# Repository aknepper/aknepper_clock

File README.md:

# aknepper_clock
 Google HPS Clock

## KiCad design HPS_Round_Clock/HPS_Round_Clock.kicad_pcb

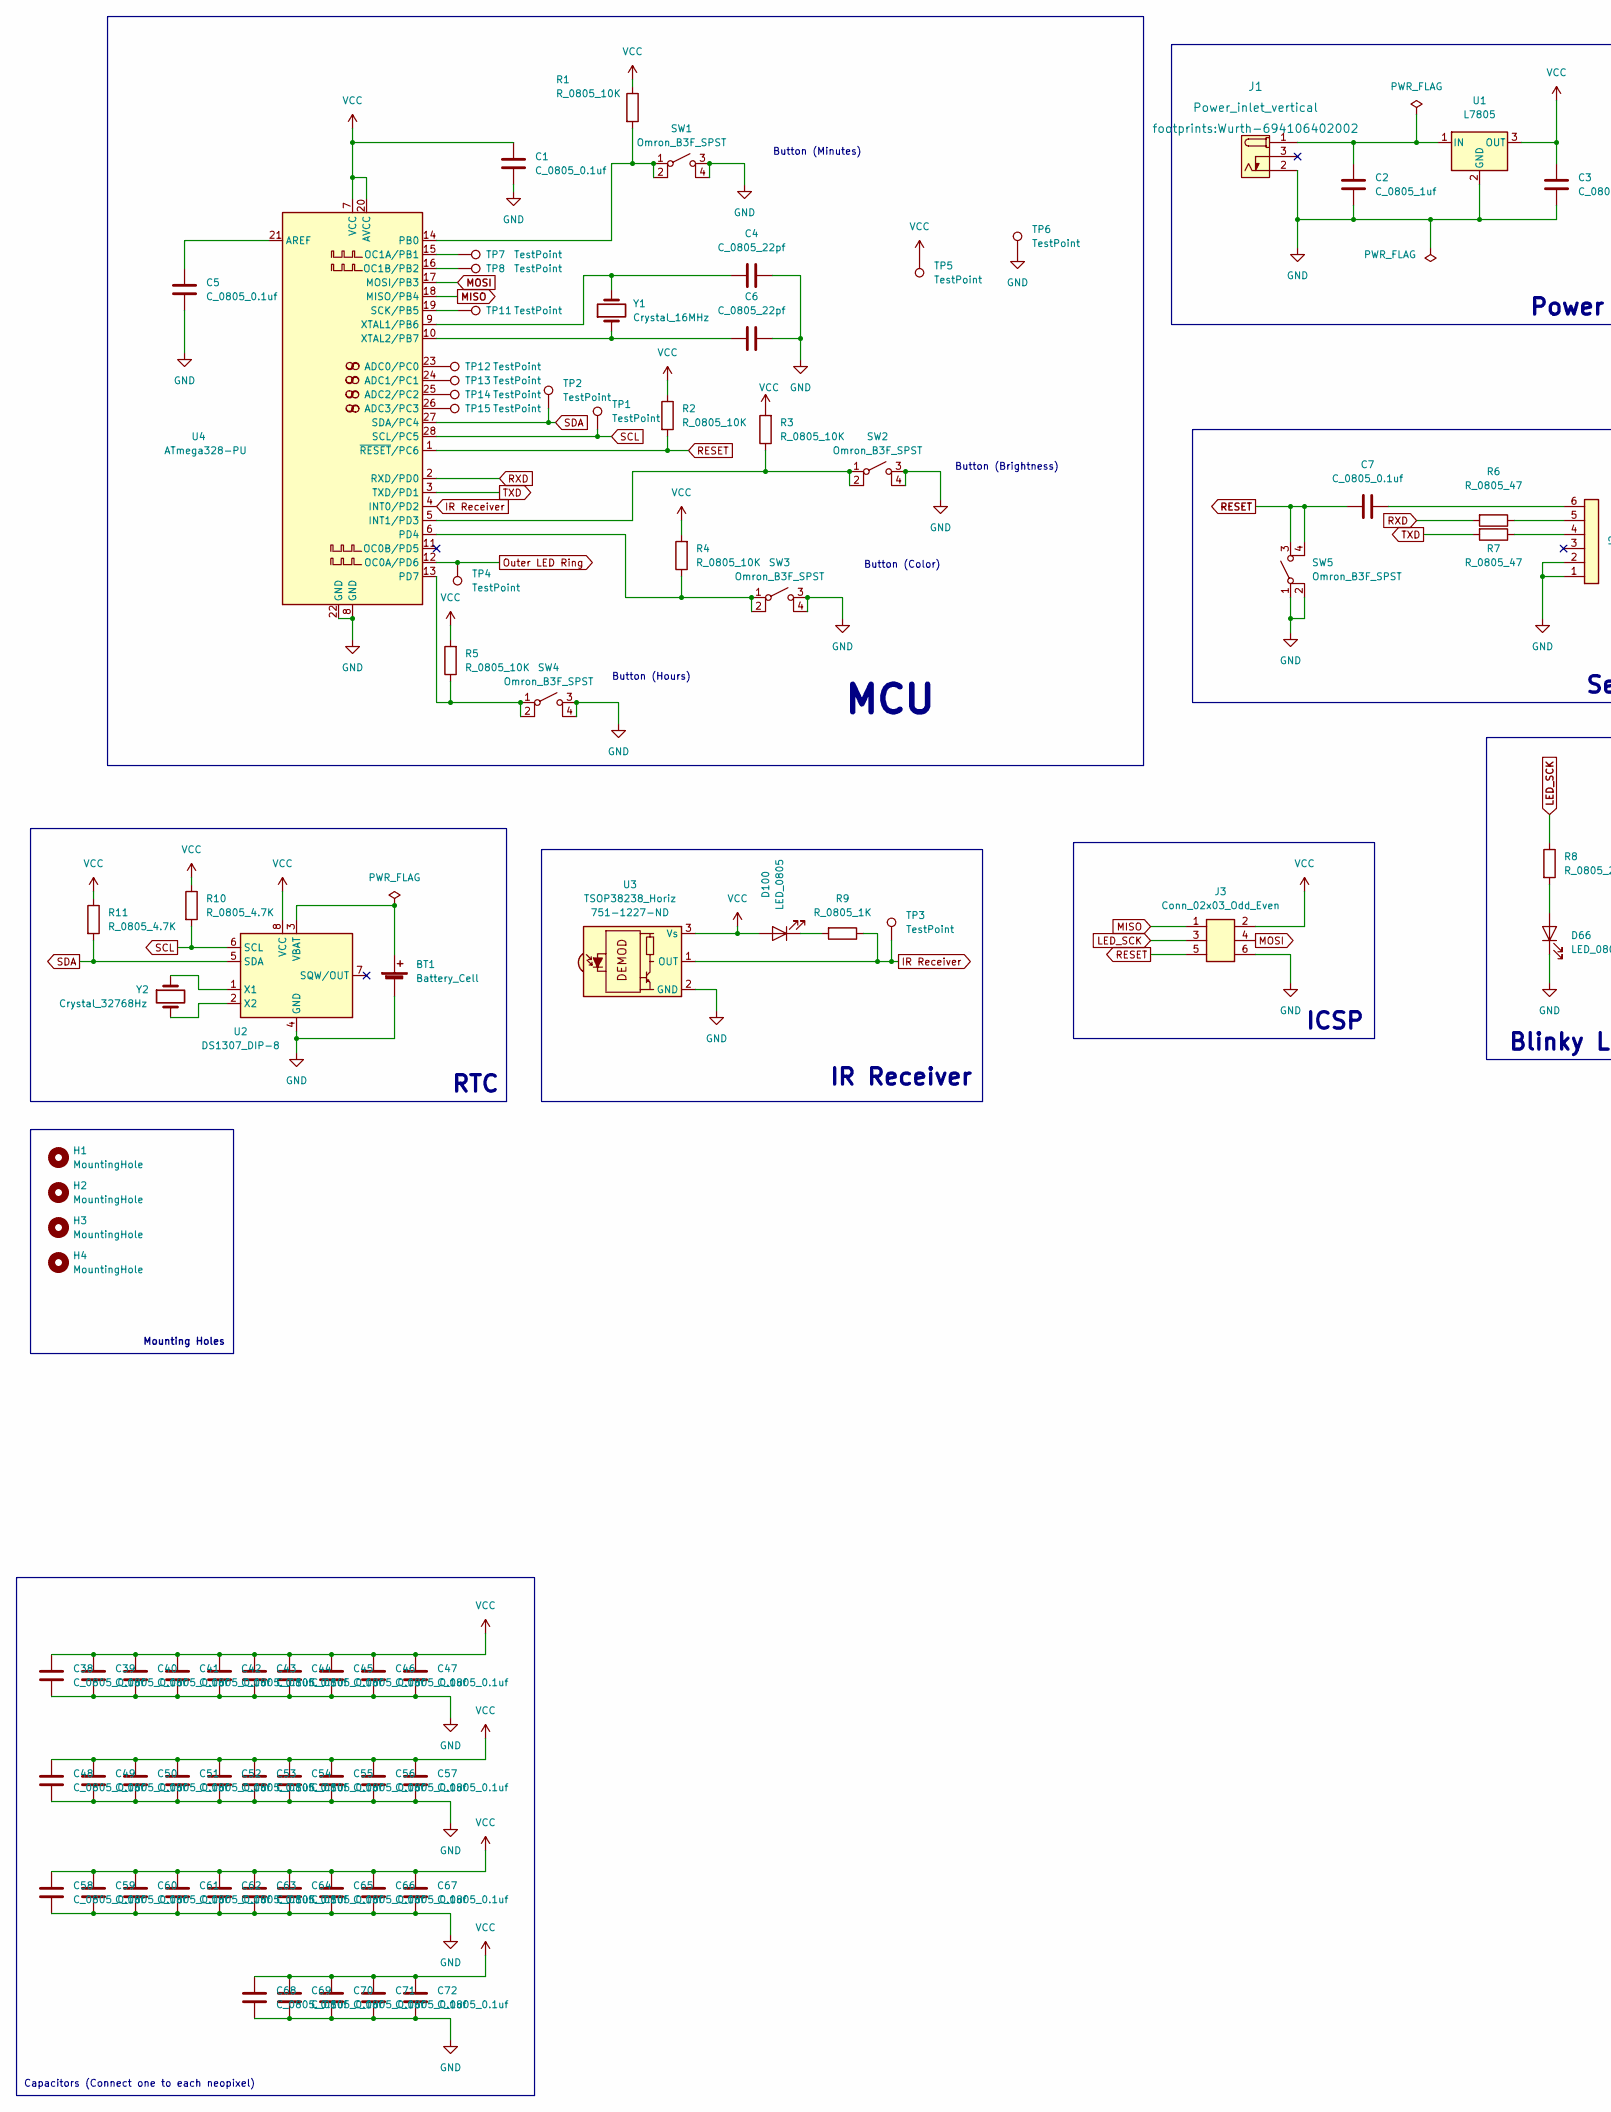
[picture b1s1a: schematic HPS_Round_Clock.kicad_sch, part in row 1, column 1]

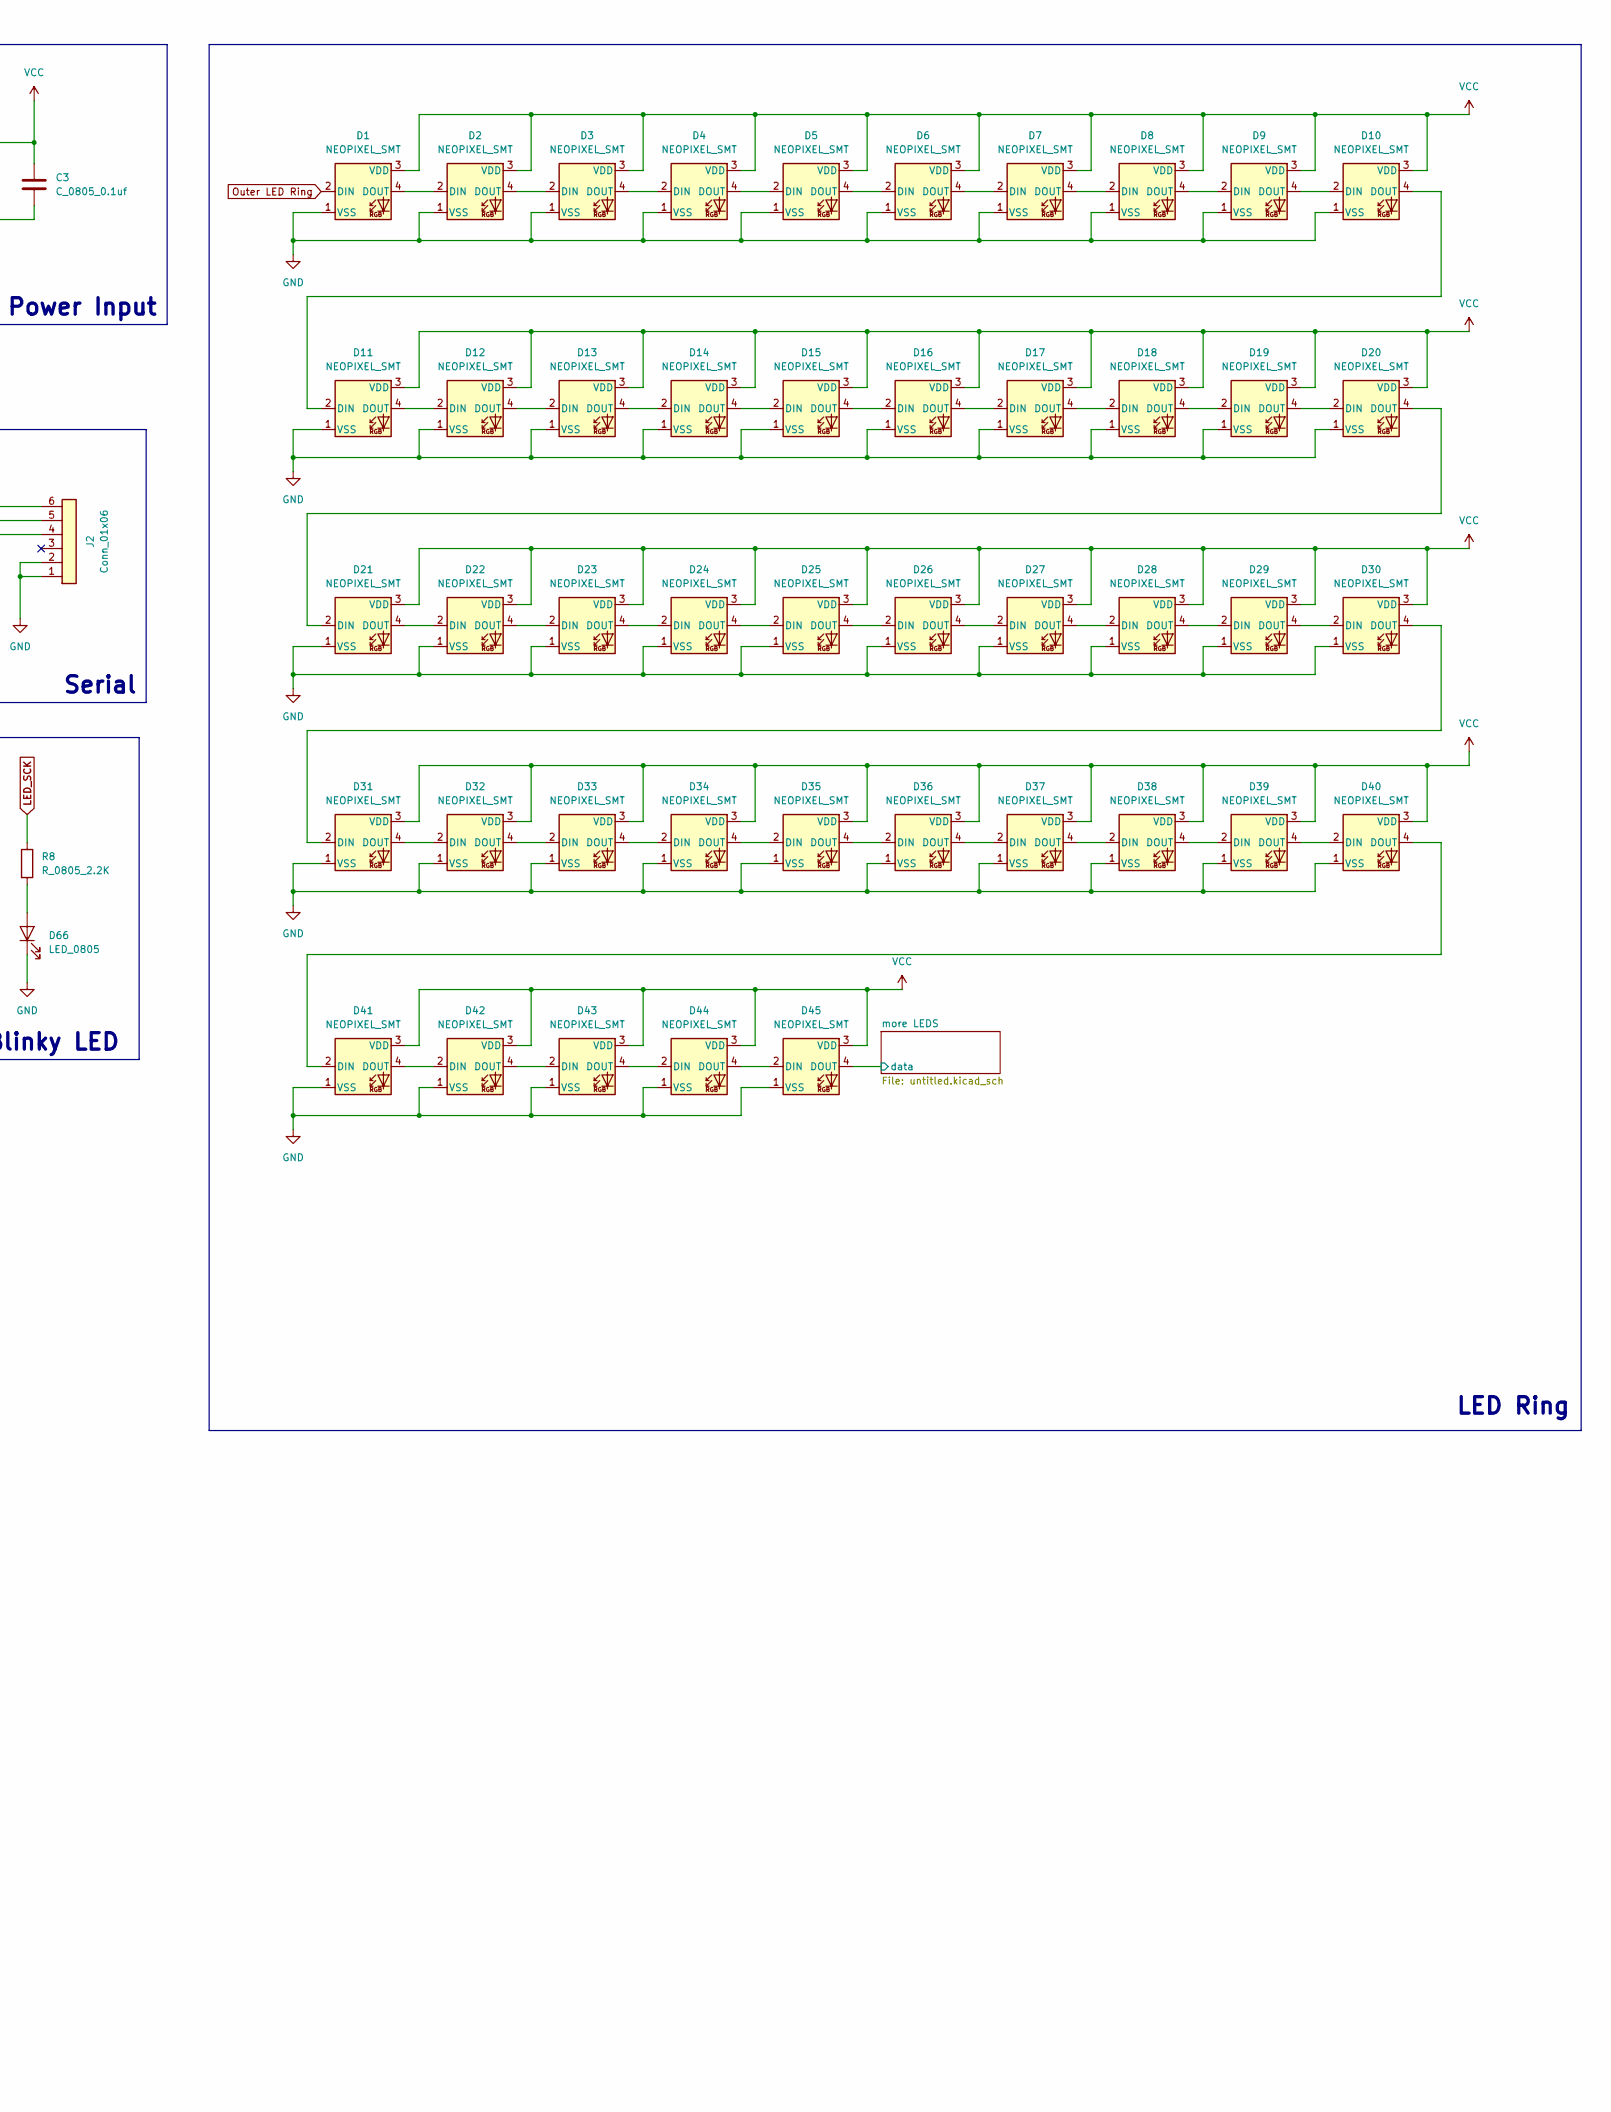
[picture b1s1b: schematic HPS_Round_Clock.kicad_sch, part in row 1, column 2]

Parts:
BT1: Battery_Cell; BatteryHolder_Keystone_106_1x20mm; MPN BS-7; Digikey PN BS-7-ND
C1, C3, C5, C7, C38, C39, C40, C41, C42, C43, C44, C45, C46, C47, C48, C49, C50, C51, C52, C53, C54, C55, C56, C57, C58, C59, C60, C61, C62, C63, C64, C65, C66, C67, C68, C69, C70, C71, C72: C_0805_0.1uf; C_0805_2012Metric; Voltage N/A; Tolerance N/A; MPN 08055C104KAT2A; Digikey PN 478-1395-1-ND
C2: C_0805_1uf; C_0805_2012Metric; Voltage N/A; Tolerance N/A; MPN CC0805KKX7R8BB105; Digikey PN 311-1456-1-ND
C4, C6: C_0805_22pf; C_0805_2012Metric; Voltage N/A; Tolerance N/A; MPN CC0805JRNPO9BN220; Digikey PN 311-1103-1-ND
D1, D2, D3, D4, D5, D6, D7, D8, D9, D10, D11, D12, D13, D14, D15, D16, D17, D18, D19, D20, D21, D22, D23, D24, D25, D26, D27, D28, D29, D30, D31, D32, D33, D34, D35, D36, D37, D38, D39, D40, D41, D42, D43, D44, D45: NEOPIXEL_SMT; LED_SK6812_PLCC4_5.0x5.0mm_P3.2mm; MPN IN-PI554FCH; Digikey PN 1830-1106-1-ND
D66, D100: LED_0805; LED_0805_2012Metric; MPN 150080RS75000; Digikey PN 732-4984-1-ND
H1, H2, H3, H4: MountingHole; MountingHole_3.2mm_M3
J1: Power_inlet_vertical; Wurth-694106402002; MPN 694106402002; Digikey PN 732-5931-ND
J2: Conn_01x06; PinHeader_1x06_P2.54mm_Vertical; MPN 61300611121; Digikey PN 732-5319-ND
J3: Conn_02x03_Odd_Even; PinHeader_2x03_P2.54mm_Vertical; MPN PRPC003DAAN-RC; Digikey PN S2011EC-03-ND
R1, R2, R3, R4, R5: R_0805_10K; R_0805_2012Metric; Tolerance N/A; MPN RC0805FR-0710KL; Digikey PN 311-10.0KCRCT-ND
R6, R7: R_0805_47; R_0805_2012Metric; Tolerance N/A; Mouser PN N/A; Digikey PN RC0805FR-0747RL
R8: R_0805_2.2K; R_0805_2012Metric; Tolerance N/A; MPN N/A; Digikey PN 311-2.20KCRCT-ND
R9: R_0805_1K; R_0805_2012Metric; Tolerance N/A; Mouser PN N/A; Digikey PN RC0805FR-0710KL
R10, R11: R_0805_4.7K; R_0805_2012Metric; Tolerance N/A; MPN RC0805FR-074K7L; Digikey PN 311-4.70KCRCT-ND
SW1, SW2, SW3, SW4, SW5: Omron_B3F_SPST; SW_SPST_Omron_B3FS-100xP; MPN B3FS-1000P; Digikey PN SW423CT-ND
TP1, TP2, TP3, TP4, TP5, TP6, TP7, TP8, TP11, TP12, TP13, TP14, TP15: TestPoint; TestPoint_THTPad_D2.0mm_Drill1.0mm
U1: L7805; TO-252-2; MPN L7805CDT-TR; Digikey PN 497-7255-1-ND
U2: DS1307_DIP-8; DIP-8_W7.62mm; MPN A 08-LC-TT; Digikey PN AE9986-ND
U3: TSOP38238_Horiz; Vishay_MINICAST-3Pin_Horiz; Digikey PN 751-1227-ND
U4: ATmega328-PU; DIP-28_W7.62mm; MPN ED281DT; Digikey PN ED3050-5-ND
Y1: Crystal_16MHz; Crystal_SMD_HC49-SD; MPN ECS-160-20-5PXDN-TR; Digikey PN XC1299CT-ND
Y2: Crystal_32768Hz; Crystal_SMD_2Pin_3.2x1.5mm; MPN Q 0,032768-JTX310-12,5-20-T1-HMR-50K-LF; Digikey PN 1908-1314-1-ND

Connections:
/more LEDS/data: D45.4 (DOUT); also elsewhere on the board
GND: BT1.2 (-), C1.2, C2.2, C3.2, C4.1, C5.2, C6.1, C38.2, C39.2, C40.2, C41.2, C42.2, C43.2, C44.2, C45.2, C46.2, C47.2, C48.2, C49.2, C50.2, C51.2, C52.2, C53.2, C54.2, C55.2, C56.2, C57.2, C58.2, C59.2, C60.2, C61.2, C62.2, C63.2, C64.2, C65.2, C66.2, C67.2, C68.2, C69.2, C70.2, C71.2, C72.2, D1.1 (VSS), D2.1 (VSS), D3.1 (VSS), D4.1 (VSS), D5.1 (VSS), D6.1 (VSS), D7.1 (VSS), D8.1 (VSS), D9.1 (VSS), D10.1 (VSS), D11.1 (VSS), D12.1 (VSS), D13.1 (VSS), D14.1 (VSS), D15.1 (VSS), D16.1 (VSS), D17.1 (VSS), D18.1 (VSS), D19.1 (VSS), D20.1 (VSS), D21.1 (VSS), D22.1 (VSS), D23.1 (VSS), D24.1 (VSS), D25.1 (VSS), D26.1 (VSS), D27.1 (VSS), D28.1 (VSS), D29.1 (VSS), D30.1 (VSS), D31.1 (VSS), D32.1 (VSS), D33.1 (VSS), D34.1 (VSS), D35.1 (VSS), D36.1 (VSS), D37.1 (VSS), D38.1 (VSS), D39.1 (VSS), D40.1 (VSS), D41.1 (VSS), D42.1 (VSS), D43.1 (VSS), D44.1 (VSS), D45.1 (VSS), D66.1 (K), J1.2 (OUT), J2.1, J2.2, J3.6, SW1.3 (B), SW1.4 (B), SW2.3 (B), SW2.4 (B), SW3.3 (B), SW3.4 (B), SW4.3 (B), SW4.4 (B), SW5.1 (A), SW5.2 (A), TP6.1, U1.2 (GND), U2.4 (GND), U3.2 (GND), U4.8 (GND), U4.22 (GND); also elsewhere on the board
IR Receiver: R9.1, TP3.1, U3.1 (OUT), U4.4 (INT0/PD2)
LED_SCK: J3.3, R8.1
MISO: J3.1, U4.18 (MISO/PB4)
MOSI: J3.4, U4.17 (MOSI/PB3)
unnamed: BT1.1 (+), U2.3 (VBAT)
unnamed: C2.1, J1.1 (POLE), U1.1 (IN)
unnamed: C4.2, U4.9 (XTAL1/PB6), Y1.2
unnamed: C5.1, U4.21 (AREF)
unnamed: C6.2, U4.10 (XTAL2/PB7), Y1.1
unnamed: C7.1, J2.6
unnamed: D1.4 (DOUT), D2.2 (DIN)
unnamed: D2.4 (DOUT), D3.2 (DIN)
unnamed: D3.4 (DOUT), D4.2 (DIN)
unnamed: D4.4 (DOUT), D5.2 (DIN)
unnamed: D5.4 (DOUT), D6.2 (DIN)
unnamed: D6.4 (DOUT), D7.2 (DIN)
unnamed: D7.4 (DOUT), D8.2 (DIN)
unnamed: D8.4 (DOUT), D9.2 (DIN)
unnamed: D9.4 (DOUT), D10.2 (DIN)
unnamed: D10.4 (DOUT), D11.2 (DIN)
unnamed: D11.4 (DOUT), D12.2 (DIN)
unnamed: D12.4 (DOUT), D13.2 (DIN)
unnamed: D13.4 (DOUT), D14.2 (DIN)
unnamed: D14.4 (DOUT), D15.2 (DIN)
unnamed: D15.4 (DOUT), D16.2 (DIN)
unnamed: D16.4 (DOUT), D17.2 (DIN)
unnamed: D17.4 (DOUT), D18.2 (DIN)
unnamed: D18.4 (DOUT), D19.2 (DIN)
unnamed: D19.4 (DOUT), D20.2 (DIN)
unnamed: D20.4 (DOUT), D21.2 (DIN)
unnamed: D21.4 (DOUT), D22.2 (DIN)
unnamed: D22.4 (DOUT), D23.2 (DIN)
unnamed: D23.4 (DOUT), D24.2 (DIN)
unnamed: D24.4 (DOUT), D25.2 (DIN)
unnamed: D25.4 (DOUT), D26.2 (DIN)
unnamed: D26.4 (DOUT), D27.2 (DIN)
unnamed: D27.4 (DOUT), D28.2 (DIN)
unnamed: D28.4 (DOUT), D29.2 (DIN)
unnamed: D29.4 (DOUT), D30.2 (DIN)
unnamed: D30.4 (DOUT), D31.2 (DIN)
unnamed: D31.4 (DOUT), D32.2 (DIN)
unnamed: D32.4 (DOUT), D33.2 (DIN)
unnamed: D33.4 (DOUT), D34.2 (DIN)
unnamed: D34.4 (DOUT), D35.2 (DIN)
unnamed: D35.4 (DOUT), D36.2 (DIN)
unnamed: D36.4 (DOUT), D37.2 (DIN)
unnamed: D37.4 (DOUT), D38.2 (DIN)
unnamed: D38.4 (DOUT), D39.2 (DIN)
unnamed: D39.4 (DOUT), D40.2 (DIN)
unnamed: D40.4 (DOUT), D41.2 (DIN)
unnamed: D41.4 (DOUT), D42.2 (DIN)
unnamed: D42.4 (DOUT), D43.2 (DIN)
unnamed: D43.4 (DOUT), D44.2 (DIN)
unnamed: D44.4 (DOUT), D45.2 (DIN)
unnamed: D66.2 (A), R8.2
unnamed: D100.1 (K), R9.2
unnamed: J2.4, R7.1
unnamed: J2.5, R6.1
unnamed: R1.2, SW1.1 (A), SW1.2 (A), U4.14 (PB0)
unnamed: R3.1, SW2.1 (A), SW2.2 (A), U4.5 (INT1/PD3)
unnamed: R4.1, SW3.1 (A), SW3.2 (A), U4.6 (PD4)
unnamed: R5.1, SW4.1 (A), SW4.2 (A), U4.13 (PD7)
unnamed: TP7.1, U4.15 (OC1A/PB1)
unnamed: TP8.1, U4.16 (OC1B/PB2)
unnamed: TP11.1, U4.19 (SCK/PB5)
unnamed: TP12.1, U4.23 (ADC0/PC0)
unnamed: TP13.1, U4.24 (ADC1/PC1)
unnamed: TP14.1, U4.25 (ADC2/PC2)
unnamed: TP15.1, U4.26 (ADC3/PC3)
unnamed: U2.1 (X1), Y2.1
unnamed: U2.2 (X2), Y2.2
Outer LED Ring: D1.2 (DIN), TP4.1, U4.12 (OC0A/PD6)
RESET: C7.2, J3.5, R2.2, SW5.3 (B), SW5.4 (B), U4.1 (~RESET/PC6)
RXD: R6.2, U4.2 (RXD/PD0)
SCL: R10.2, TP1.1, U2.6 (SCL), U4.28 (SCL/PC5)
SDA: R11.2, TP2.1, U2.5 (SDA), U4.27 (SDA/PC4)
TXD: R7.2, U4.3 (TXD/PD1)
VCC: C1.1, C3.1, C38.1, C39.1, C40.1, C41.1, C42.1, C43.1, C44.1, C45.1, C46.1, C47.1, C48.1, C49.1, C50.1, C51.1, C52.1, C53.1, C54.1, C55.1, C56.1, C57.1, C58.1, C59.1, C60.1, C61.1, C62.1, C63.1, C64.1, C65.1, C66.1, C67.1, C68.1, C69.1, C70.1, C71.1, C72.1, D1.3 (VDD), D2.3 (VDD), D3.3 (VDD), D4.3 (VDD), D5.3 (VDD), D6.3 (VDD), D7.3 (VDD), D8.3 (VDD), D9.3 (VDD), D10.3 (VDD), D11.3 (VDD), D12.3 (VDD), D13.3 (VDD), D14.3 (VDD), D15.3 (VDD), D16.3 (VDD), D17.3 (VDD), D18.3 (VDD), D19.3 (VDD), D20.3 (VDD), D21.3 (VDD), D22.3 (VDD), D23.3 (VDD), D24.3 (VDD), D25.3 (VDD), D26.3 (VDD), D27.3 (VDD), D28.3 (VDD), D29.3 (VDD), D30.3 (VDD), D31.3 (VDD), D32.3 (VDD), D33.3 (VDD), D34.3 (VDD), D35.3 (VDD), D36.3 (VDD), D37.3 (VDD), D38.3 (VDD), D39.3 (VDD), D40.3 (VDD), D41.3 (VDD), D42.3 (VDD), D43.3 (VDD), D44.3 (VDD), D45.3 (VDD), D100.2 (A), J3.2, R1.1, R2.1, R3.2, R4.2, R5.2, R10.1, R11.1, TP5.1, U1.3 (OUT), U2.8 (VCC), U3.3 (Vs), U4.7 (VCC), U4.20 (AVCC); also elsewhere on the board

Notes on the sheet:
MCU
Mounting Holes
LED Ring
Serial
Power Input
Blinky LED
IR Receiver
ICSP
Capacitors (Connect one to each neopixel)
Button (Brightness)
RTC
Button (Hours)
Button (Minutes)
Button (Color)

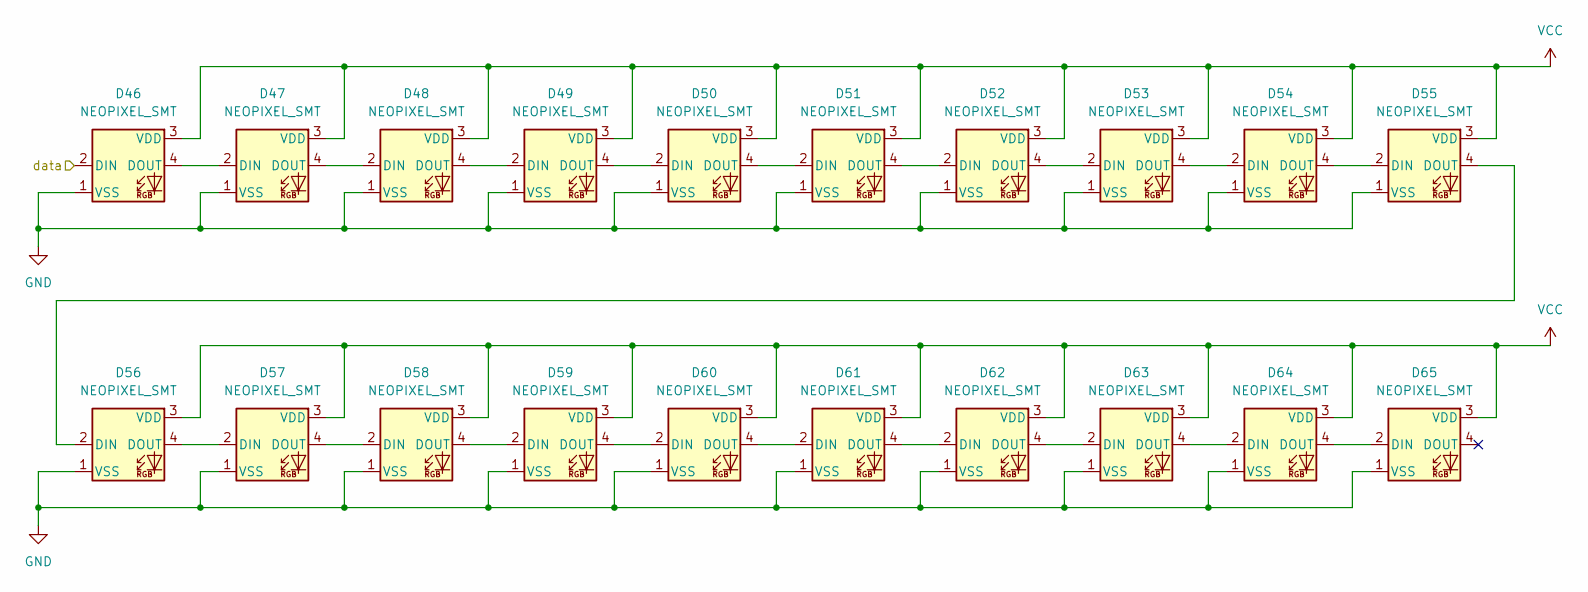
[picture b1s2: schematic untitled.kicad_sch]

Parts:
D46, D47, D48, D49, D50, D51, D52, D53, D54, D55, D56, D57, D58, D59, D60, D61, D62, D63, D64, D65: NEOPIXEL_SMT; LED_SK6812_PLCC4_5.0x5.0mm_P3.2mm; MPN IN-PI554FCH; Digikey PN 1830-1106-1-ND

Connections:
/more LEDS/data: D46.2 (DIN); also elsewhere on the board
GND: D46.1 (VSS), D47.1 (VSS), D48.1 (VSS), D49.1 (VSS), D50.1 (VSS), D51.1 (VSS), D52.1 (VSS), D53.1 (VSS), D54.1 (VSS), D55.1 (VSS), D56.1 (VSS), D57.1 (VSS), D58.1 (VSS), D59.1 (VSS), D60.1 (VSS), D61.1 (VSS), D62.1 (VSS), D63.1 (VSS), D64.1 (VSS), D65.1 (VSS); also elsewhere on the board
unnamed: D46.4 (DOUT), D47.2 (DIN)
unnamed: D47.4 (DOUT), D48.2 (DIN)
unnamed: D48.4 (DOUT), D49.2 (DIN)
unnamed: D49.4 (DOUT), D50.2 (DIN)
unnamed: D50.4 (DOUT), D51.2 (DIN)
unnamed: D51.4 (DOUT), D52.2 (DIN)
unnamed: D52.4 (DOUT), D53.2 (DIN)
unnamed: D53.4 (DOUT), D54.2 (DIN)
unnamed: D54.4 (DOUT), D55.2 (DIN)
unnamed: D55.4 (DOUT), D56.2 (DIN)
unnamed: D56.4 (DOUT), D57.2 (DIN)
unnamed: D57.4 (DOUT), D58.2 (DIN)
unnamed: D58.4 (DOUT), D59.2 (DIN)
unnamed: D59.4 (DOUT), D60.2 (DIN)
unnamed: D60.4 (DOUT), D61.2 (DIN)
unnamed: D61.4 (DOUT), D62.2 (DIN)
unnamed: D62.4 (DOUT), D63.2 (DIN)
unnamed: D63.4 (DOUT), D64.2 (DIN)
unnamed: D64.4 (DOUT), D65.2 (DIN)
VCC: D46.3 (VDD), D47.3 (VDD), D48.3 (VDD), D49.3 (VDD), D50.3 (VDD), D51.3 (VDD), D52.3 (VDD), D53.3 (VDD), D54.3 (VDD), D55.3 (VDD), D56.3 (VDD), D57.3 (VDD), D58.3 (VDD), D59.3 (VDD), D60.3 (VDD), D61.3 (VDD), D62.3 (VDD), D63.3 (VDD), D64.3 (VDD), D65.3 (VDD); also elsewhere on the board

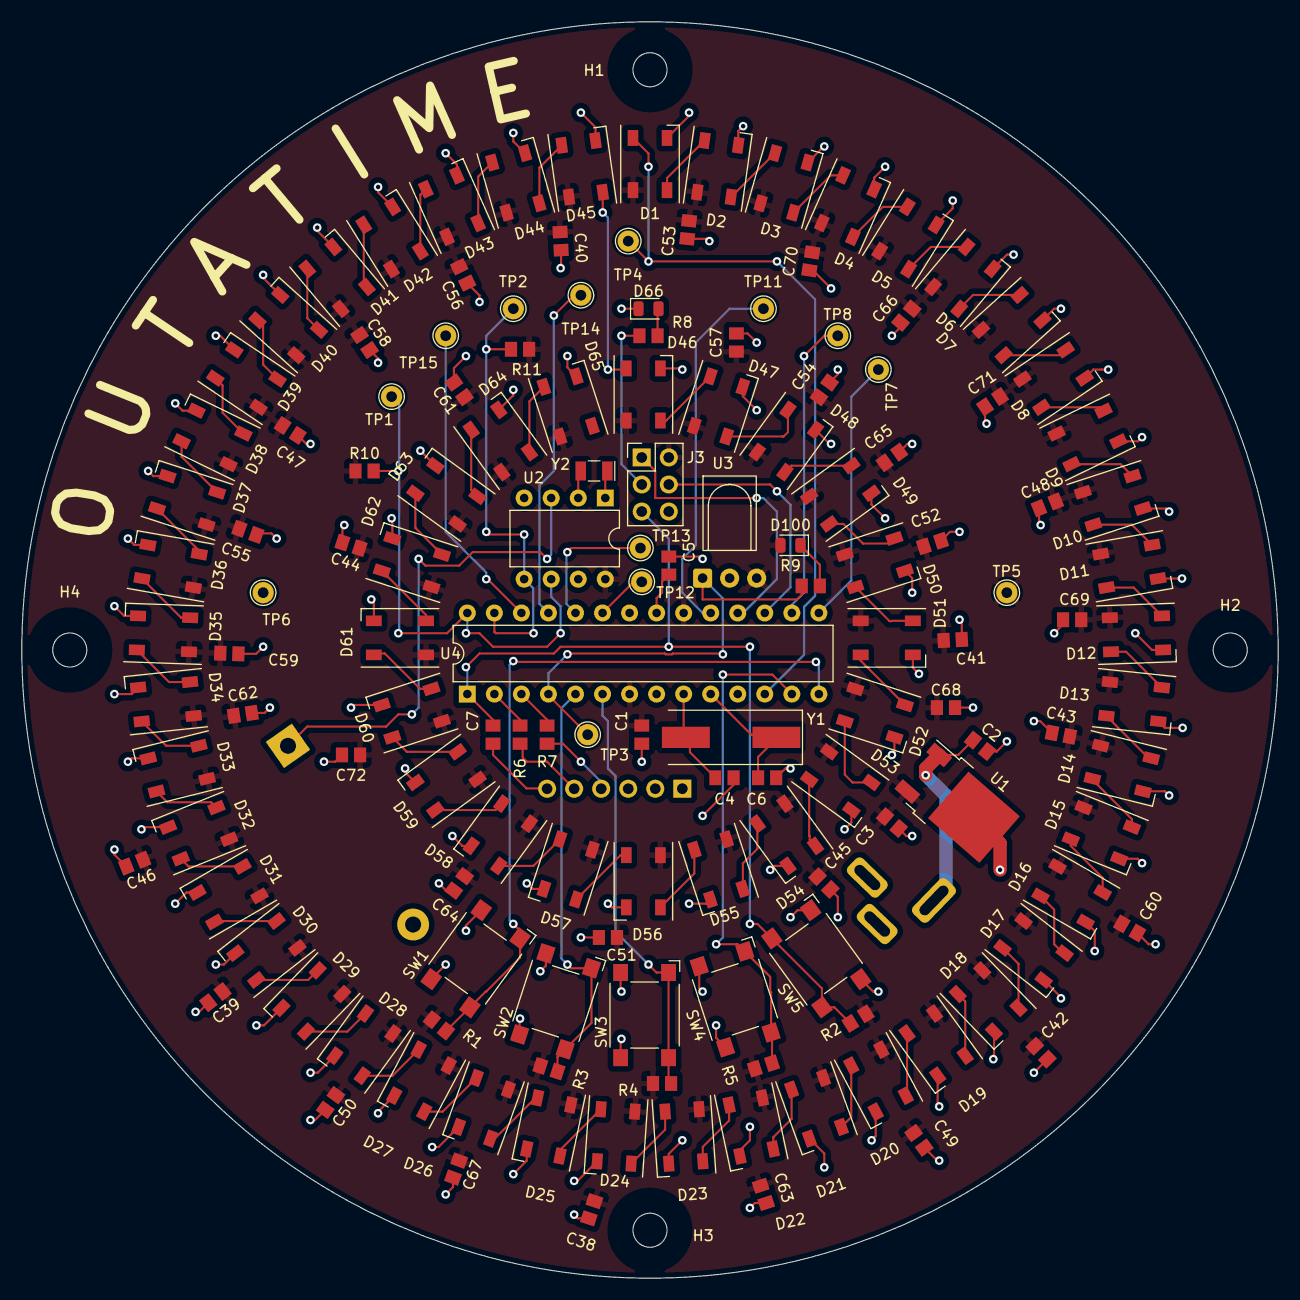
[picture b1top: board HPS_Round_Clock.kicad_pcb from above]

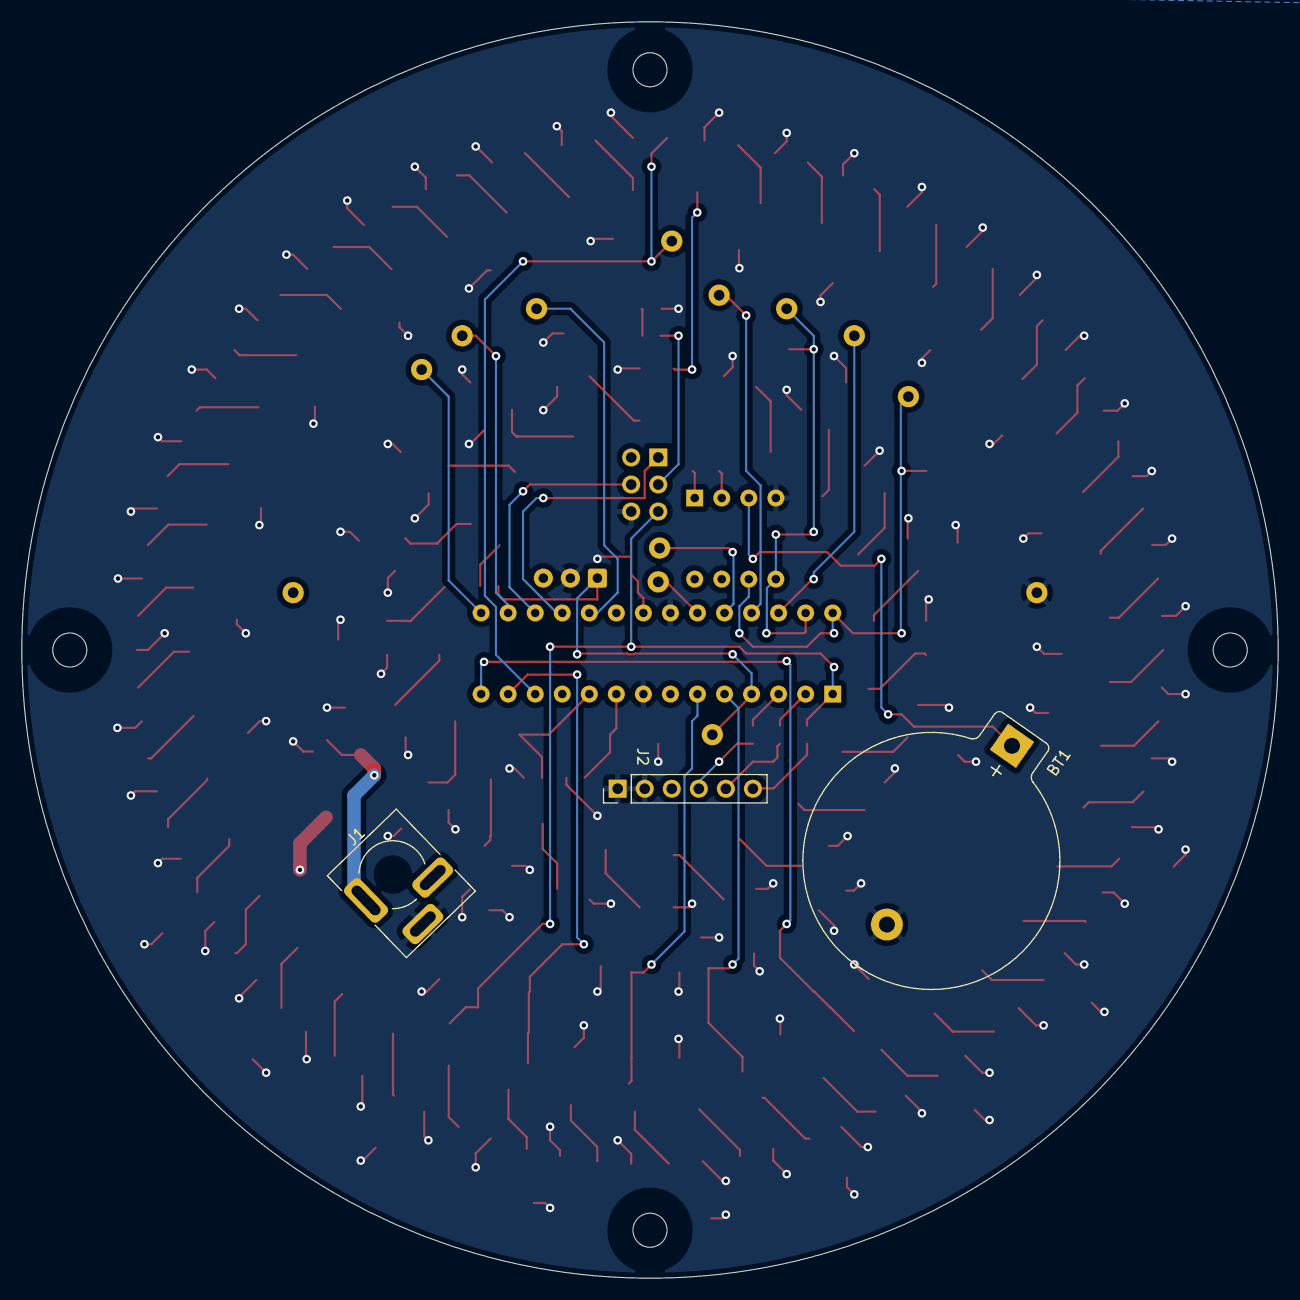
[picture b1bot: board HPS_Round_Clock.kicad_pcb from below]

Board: 2 copper layers, 118.0 x 118.0 mm, 152 parts (3 on the bottom side), 99 nets.

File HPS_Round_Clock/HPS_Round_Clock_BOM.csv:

"Id";"Designator";"Package";"Quantity";"Designation";"Supplier and ref";
1;"D64,D53,D49,D45,D11,D8,D25,D28,D54,D6,D10,D20,D61,D13,D21,D40,D29,D7,D3,D33,D41,D23,D38,D1,D4,D22,D31,D34,D30,D5,D26,D63,D42,D9,D44,D14,D59,D47,D12,D51,D18,D60,D16,D39,D46,D50,D48,D35,D57,D55,D17,D15,D58,D56,D2,D19,D65,D52,D27,D43,D36,D32,D24,D37,D62";"LED_SK6812_PLCC4_5.0x5.0mm_P3.2mm";65;"NEOPIXEL_SMT";;;
2;"H4,H2,H3,H1";"MountingHole_3.2mm_M3";4;"MountingHole";;;
3;"C41,C61,C43,C40,C59,C65,C57,C66,C54,C47,C53,C60,C52,C45,C64,C50,C62,C51,C70,C58,C46,C7,C71,C69,C5,C67,C48,C39,C44,C42,C56,C1,C49,C63,C55,C3,C68,C72,C38";"C_0805_2012Metric";39;"C_0805_0.1uf";;;
4;"R4,R1,R5,R2,R3";"R_0805_2012Metric";5;"R_0805_10K";;;
5;"Y1";"Crystal_SMD_HC49-SD";1;"Crystal_16MHz";;;
6;"TP11,TP13,TP4,TP15,TP5,TP2,TP8,TP1,TP14,TP3,TP12,TP6,TP7";"TestPoint_THTPad_D2.0mm_Drill1.0mm";13;"TestPoint";;;
7;"R8";"R_0805_2012Metric";1;"R_0805_2.2K";;;
8;"R9";"R_0805_2012Metric";1;"R_0805_1K";;;
9;"SW4,SW2,SW1,SW5,SW3";"SW_SPST_Omron_B3FS-100xP";5;"Omron_B3F_SPST";;;
10;"D66,D100";"LED_0805_2012Metric";2;"LED_0805";;;
11;"C6,C4";"C_0805_2012Metric";2;"C_0805_22pf";;;
12;"R10,R11";"R_0805_2012Metric";2;"R_0805_4.7K";;;
13;"R6,R7";"R_0805_2012Metric";2;"R_0805_47";;;
14;"Y2";"Crystal_SMD_2Pin_3.2x1.5mm";1;"Crystal_32768Hz";;;
15;"U4";"DIP-28_W7.62mm";1;"ATmega328-PU";;;
16;"U1";"TO-252-2";1;"L7805";;;
17;"U3";"Vishay_MINICAST-3Pin_Horiz";1;"TSOP38238_Horiz";;;
18;"U2";"DIP-8_W7.62mm";1;"DS1307_DIP-8";;;
19;"C2";"C_0805_2012Metric";1;"C_0805_1uf";;;
20;"J3";"PinHeader_2x03_P2.54mm_Vertical";1;"Conn_02x03_Odd_Even";;;
21;"BT1";"BatteryHolder_Keystone_106_1x20mm";1;"Battery_Cell";;;
22;"J2";"PinHeader_1x06_P2.54mm_Vertical";1;"Conn_01x06";;;
23;"J1";"Wurth-694106402002";1;"Power_inlet_vertical";;;

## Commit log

2022-06-05 Round Clock
2022-06-09 Create fp-info-cache
2022-07-21 Full Gerber Push
2022-07-30 Firmware Tests
2022-08-23 clock update
